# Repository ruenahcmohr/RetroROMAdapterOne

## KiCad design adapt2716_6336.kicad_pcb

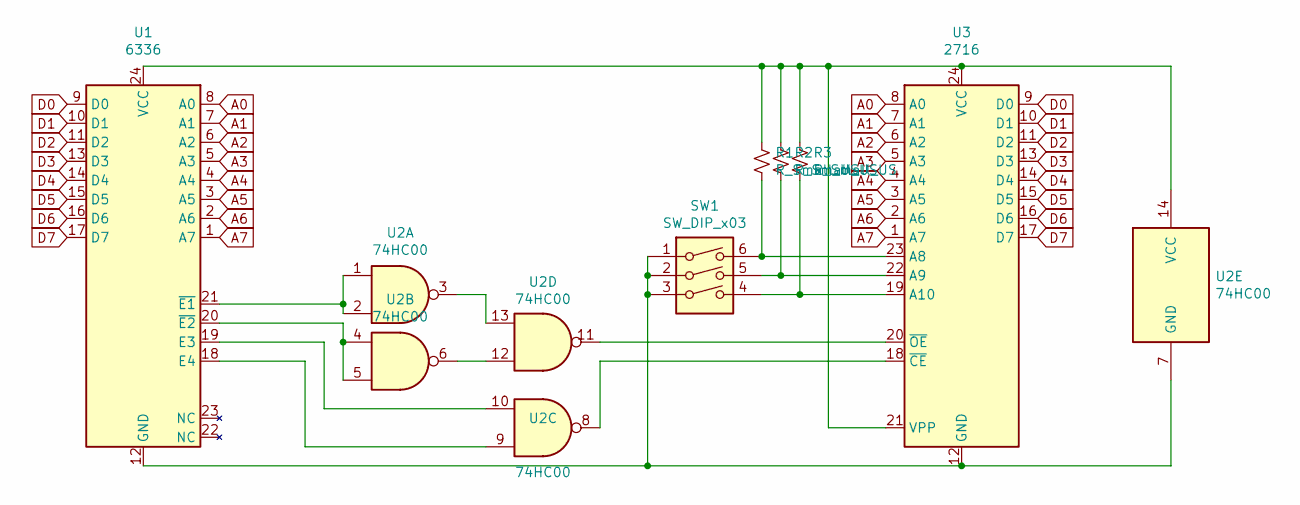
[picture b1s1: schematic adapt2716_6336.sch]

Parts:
R1, R2, R3: R_Small_US; R_0805_2012Metric_Pad1.15x1.40mm_HandSolder
SW1: SW_DIP_x03; DIP-6_W7.62mm_LongPads
U1: 6336; DIP-24_W15.24mm
U2: 74HC00; SOIC-14_3.9x8.7mm_P1.27mm
U3: 2716; DIP-24_W15.24mm

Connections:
A0: U1.8 (A0), U3.8 (A0)
A1: U1.7 (A1), U3.7 (A1)
A2: U1.6 (A2), U3.6 (A2)
A3: U1.5 (A3), U3.5 (A3)
A4: U1.4 (A4), U3.4 (A4)
A5: U1.3 (A5), U3.3 (A5)
A6: U1.2 (A6), U3.2 (A6)
A7: U1.1 (A7), U3.1 (A7)
D0: U1.9 (D0), U3.9 (D0)
D1: U1.10 (D1), U3.10 (D1)
D2: U1.11 (D2), U3.11 (D2)
D3: U1.13 (D3), U3.13 (D3)
D4: U1.14 (D4), U3.14 (D4)
D5: U1.15 (D5), U3.15 (D5)
D6: U1.16 (D6), U3.16 (D6)
D7: U1.17 (D7), U3.17 (D7)
unnamed: R1.1, R2.1, R3.1, U1.24 (VCC), U2.14 (VCC), U3.21 (VPP), U3.24 (VCC)
unnamed: R1.2, SW1.6, U3.23 (A8)
unnamed: R2.2, SW1.5, U3.22 (A9)
unnamed: R3.2, SW1.4, U3.19 (A10)
unnamed: SW1.1, SW1.2, SW1.3, U1.12 (GND), U2.7 (GND), U3.12 (GND)
unnamed: U1.18 (E4), U2.9
unnamed: U1.19 (E3), U2.10
unnamed: U1.20 (~E2), U2.4, U2.5
unnamed: U1.21 (~E1), U2.1, U2.2
unnamed: U2.8, U3.18 (~CE)
unnamed: U2.11, U3.20 (~OE)
unnamed: U2.6, U2.12
unnamed: U2.3, U2.13

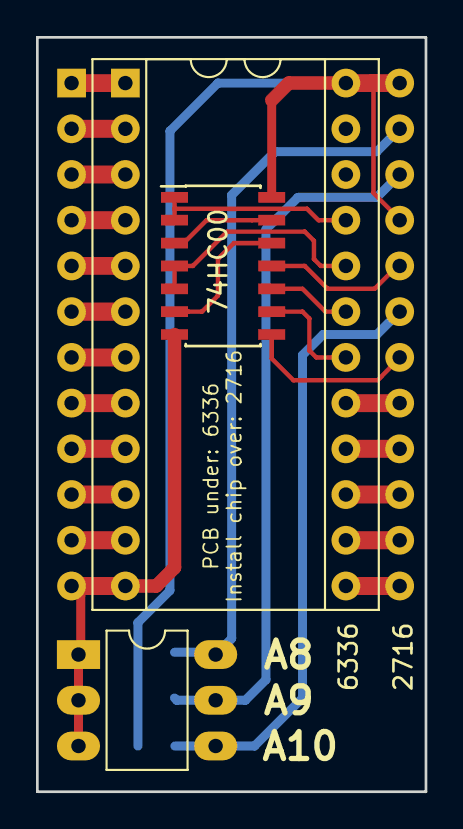
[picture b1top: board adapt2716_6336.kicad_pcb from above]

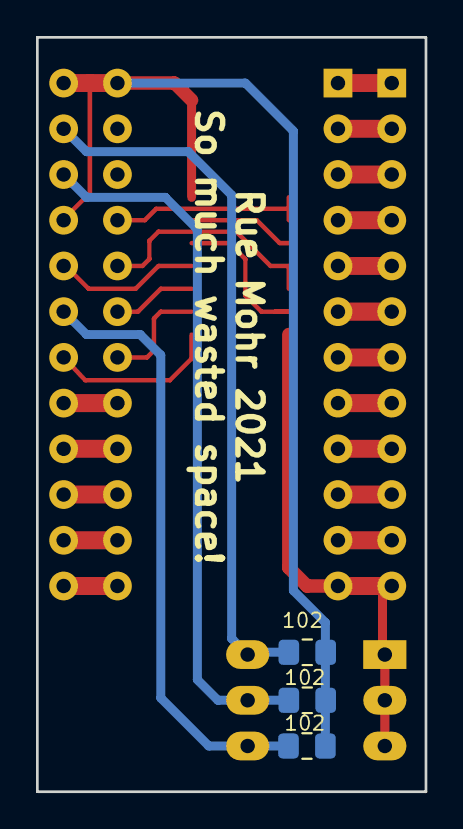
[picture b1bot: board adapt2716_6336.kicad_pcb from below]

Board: 2 copper layers, 21.6 x 41.9 mm, 7 parts (3 on the bottom side), 29 nets.

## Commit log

2021-09-15 initial upload
